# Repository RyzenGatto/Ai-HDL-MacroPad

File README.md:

# AI-HDL-MacroPad
Application Specific nRF52840 OR RP2040 based Keyboards for the PRISM Lab at the University of Arizona

Below are 3D renders. Schematic for the latest version is available in the Repo.

NOTE: If you want to adapt this to your own project with more keys, get familiar with KiCad and learn keyboard matrices (KMK has a good guide in their repo). 

## Info

KiCad files can be found in its folder. Production files can be found in Export Files. Version 1 is a super simple 5-key design for use with a XIAO RP2040. It does not have Bluetooth. It's also much cheaper. 
Version 1.5 has BT and a lithium-ion battery and relies on the KMK firmware.

## Version 2.4 
Fully integrated Macro Design. This design has been optimized for long-term reliability and has been simplified. A test PCB is accessible in the V2 kicad folders

## Old Versions
**Version 1**
This is the cheapest version. It can be assembled by hand, no BOM or pick and place needed.

**Version 1.5**
Basically V1 but with BLE and a battery and M2 2.2mm screws.

**Version 2.3 (Test PCB)**

# TO DO

1. Write software using KMK firmware

~~2. Determine Key Caps~~ DONE

~~3. Develop wifi version with battery + BT~~ DONE

4.  PROTOTYPE!

# Materials
ONLY FOR V1.5
| Item  | Quantity | Link |
| ------------- | ------------- | ---- |
| seeed studio XIAO nRF52840  | 1  | [Mouser](https://www.mouser.com/ProductDetail/Seeed-Studio/102010448?qs=Znm5pLBrcAJ5g%252BWAkitg4w%3D%3D)     |
| Cherry MX Switches  | 6  |  [Mouser](https://www.mouser.com/ProductDetail/CHERRY/MX1A-C1NW?qs=sGAEpiMZZMtFyPk3yBMYYJ6eFtqPPgccKDEfiw%252Brqds%3D)    |
| Lithium-Ion Battery | 1 | [Option 1](https://www.digikey.com/en/products/detail/sparkfun-electronics/PRT-13851/6605199) [Option 2](https://www.digikey.com/en/products/detail/adafruit-industries-llc/258/5054544) |
| Battery connector | 1 | [Mouser](https://www.digikey.com/en/products/detail/jst-sales-america-inc/S2B-PH-K-S/926626) |
| Battery LED | 1 | [Mouser](https://www.digikey.com/en/products/detail/sparkfun-electronics/COM-16347/11630204)

2.xx Materials are available in the BOM of the KiCad Files.

# Firmware

This project will use the [KMK Firmware](https://github.com/KMKfw/kmk_firmware).
KMK has its own license, please refer to their page for more details. KMK has a GUI interface that another developer made.

This [battery management](https://github.com/Tjoms99/xiao_sense_nrf52840_battery_lib) software will be used to communicate battery life and charge status to the user.

Software by [this guy](https://github.com/ernesto-martinez1)

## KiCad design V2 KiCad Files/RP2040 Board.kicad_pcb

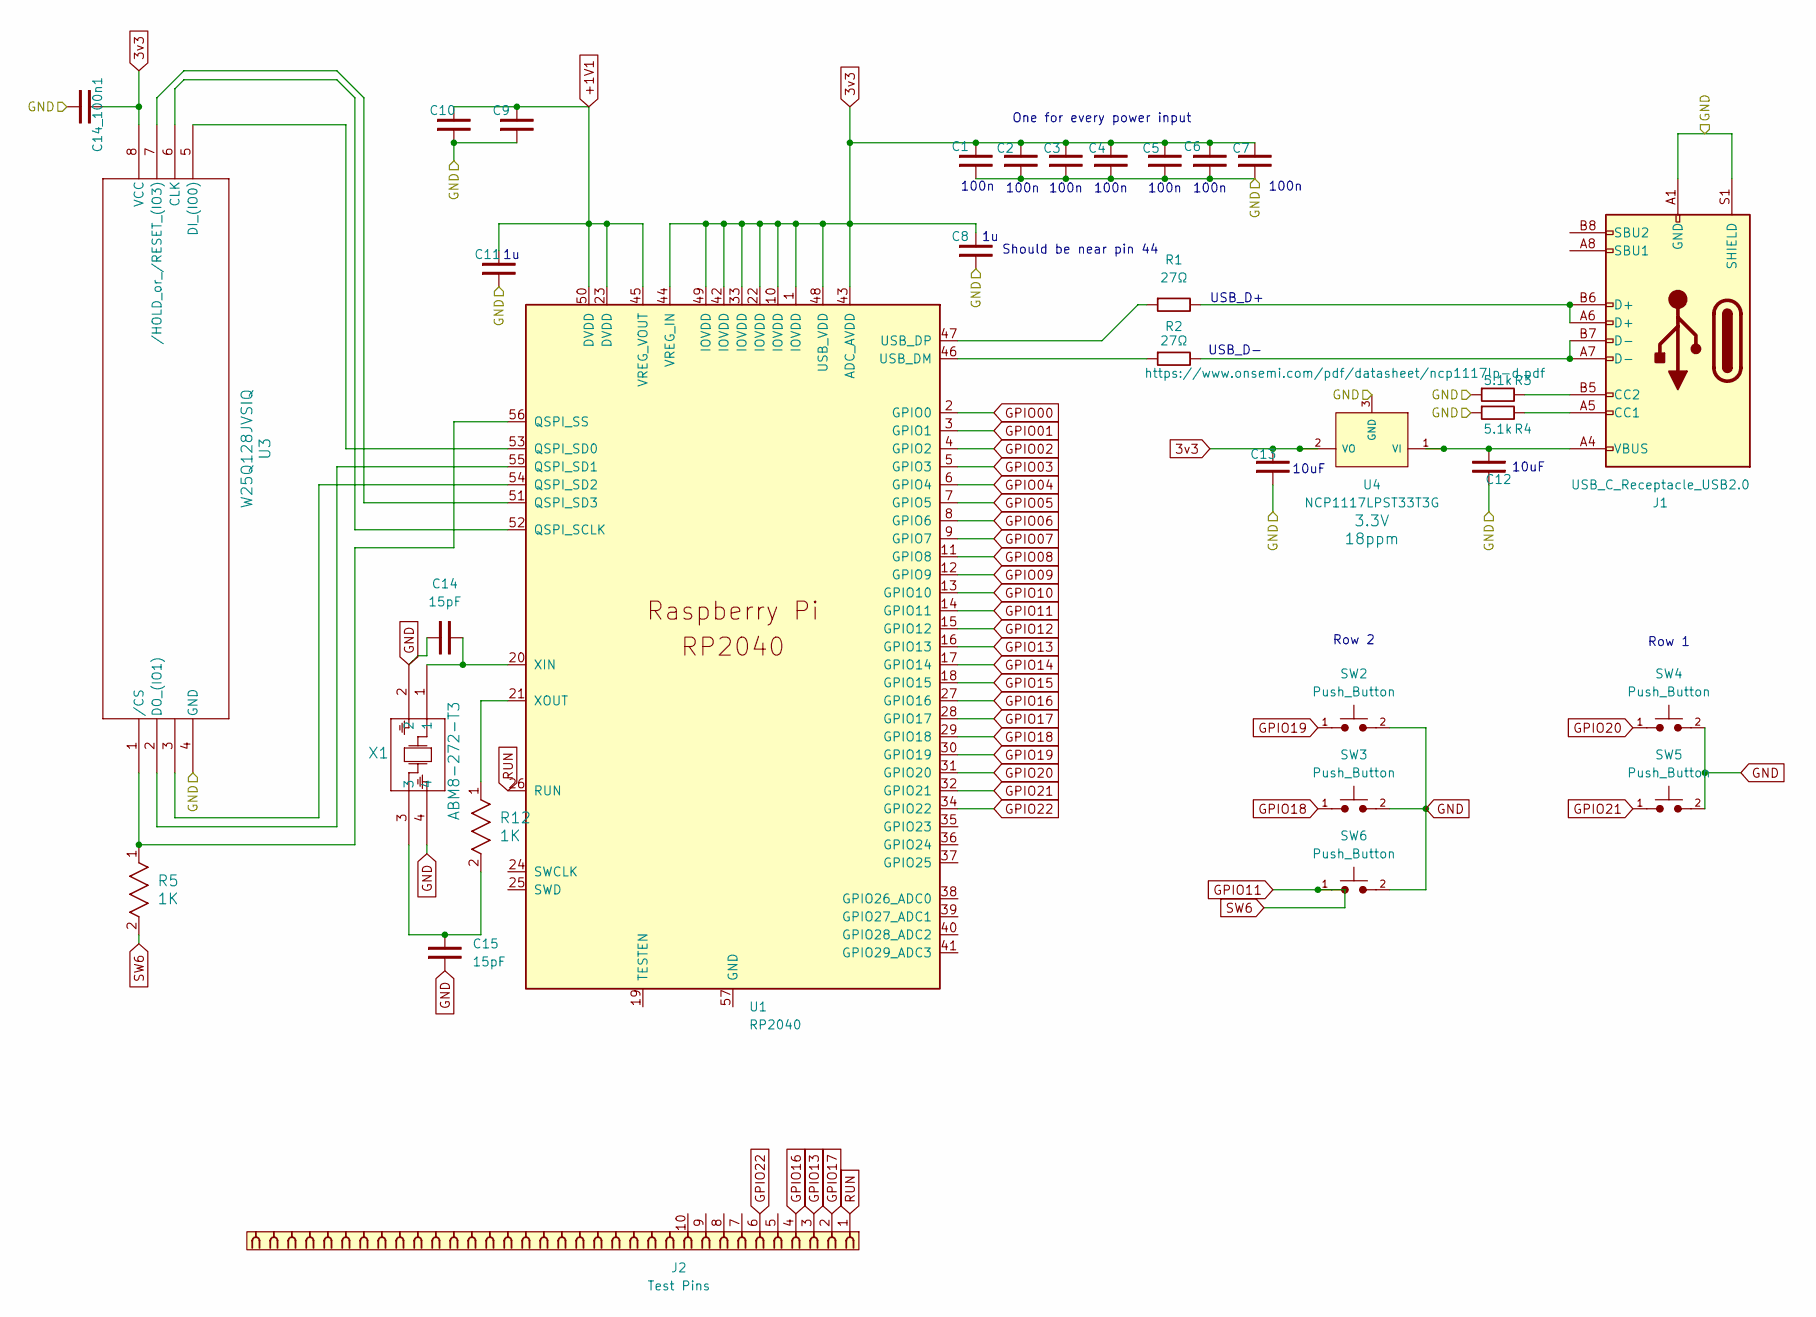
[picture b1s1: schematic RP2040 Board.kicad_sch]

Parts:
C1, C2, C3, C4, C5, C6, C7, C9, C10, C14_100n1: 100nF; C_0603_1608Metric; Part Number CL10E104KC8VPNC
C8, C11: 1uF; C_0603_1608Metric; Part Number CL10B105KP8NNNC
C12, C13: 10uF; C_0603_1608Metric; Part Number CL10A106MQ8NNNC
C14, C15: 15pF; C_0603_1608Metric; Part Number 885012006003
J1: USB_C_Receptacle_USB2.0; USB_C_Receptacle_G-Switch_GT-USB-7010ASV; Part Number GT-USB-7010ASV; LCSC C165948
J2: Test Pins
R1, R2: 27Ω; R_0402_1005Metric; Part Number ERJ-2RKF27R0X
R3, R4: 5.1k; R_0402_1005Metric; Part Number ERA-2AEB512X
R5, R12: 1K; RC0402N_PAN; Part Number ERJ-2RKF1001X
SW2, SW3, SW4, SW5, SW6: Push_Button; SW_Cherry_MX_1.00u_PCB; Part Number MX1A-C1NW
U1: RP2040; RP2040-QFN-56; Part Number SC0914(13)
U3: W25Q128JVSIQ; SOIC-8-1EP_3.9x4.9mm_P1.27mm_EP2.29x3mm; Part Number W25Q128JVSIQ
U4: NCP1117LPST33T3G; NCP1117; Part Number NCP1117LPST33T3G; JLCPCB ID C233715
X1: ABM8-272-T3; ABM8-272-T3_ABR; Part Number ABM8-272-T3

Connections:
3v3: C1.2, C2.2, C3.2, C4.2, C5.2, C6.2, C7.2, C8.2, C13.2, C14_100n1.2, U1.1 (IOVDD), U1.10 (IOVDD), U1.22 (IOVDD), U1.33 (IOVDD), U1.42 (IOVDD), U1.43 (ADC_AVDD), U1.44 (VREG_IN), U1.48 (USB_VDD), U1.49 (IOVDD), U3.8 (VCC), U4.2 (VO)
+1V1: C9.2, C10.2, C11.2, U1.23 (DVDD), U1.45 (VREG_VOUT), U1.50 (DVDD)
GND: C1.1, C2.1, C3.1, C4.1, C5.1, C6.1, C7.1, C8.1, C9.1, C10.1, C11.1, C12.2, C13.1, C14.1, C14_100n1.1, C15.1, J1.A1 (GND), J1.A12 (GND), J1.B1 (GND), J1.B12 (GND), J1.S1 (SHIELD), R3.1, R4.1, SW2.2, SW3.2, SW4.2, SW5.2, SW6.2, U1.57 (GND), U1.GND, U3.4 (GND), U4.3 (GND), X1.2, X1.4
GPIO00: U1.2 (GPIO0)
GPIO01: U1.3 (GPIO1)
GPIO02: U1.4 (GPIO2)
GPIO03: U1.5 (GPIO3)
GPIO04: U1.6 (GPIO4)
GPIO05: U1.7 (GPIO5)
GPIO06: U1.8 (GPIO6)
GPIO07: U1.9 (GPIO7)
GPIO08: U1.11 (GPIO8)
GPIO09: U1.12 (GPIO9)
GPIO10: U1.13 (GPIO10)
GPIO11: R5.2, SW6.1, U1.14 (GPIO11)
GPIO12: U1.15 (GPIO12)
GPIO13: J2.3, U1.16 (GPIO13)
GPIO14: U1.17 (GPIO14)
GPIO15: U1.18 (GPIO15)
GPIO16: J2.4, U1.27 (GPIO16)
GPIO17: J2.2, U1.28 (GPIO17)
GPIO18: SW3.1, U1.29 (GPIO18)
GPIO19: SW2.1, U1.30 (GPIO19)
GPIO20: SW4.1, U1.31 (GPIO20)
GPIO21: SW5.1, U1.32 (GPIO21)
GPIO22: J2.6, U1.34 (GPIO22)
unnamed: C15.2, R12.2, X1.3
unnamed: J1.A5 (CC1), R4.2
unnamed: J1.B5 (CC2), R3.2
unnamed: J1.A6 (D+), J1.B6 (D+), R1.2
unnamed: J1.A7 (D-), J1.B7 (D-), R2.2
unnamed: U1.52 (QSPI_SCLK), U3.6 (CLK)
unnamed: U1.53 (QSPI_SD0), U3.5 (DI_(IO0))
unnamed: U1.55 (QSPI_SD1), U3.2 (DO_(IO1))
unnamed: U1.54 (QSPI_SD2), U3.3
unnamed: U1.51 (QSPI_SD3), U3.7 (/HOLD_or_/RESET_(IO3))
unnamed: R5.1, U1.56 (QSPI_SS), U3.1 (/CS)
unnamed: R2.1, U1.46 (USB_DM)
unnamed: R1.1, U1.47 (USB_DP)
unnamed: C14.2, U1.20 (XIN), X1.1
unnamed: R12.1, U1.21 (XOUT)
unnamed: C12.1, J1.A4 (VBUS), J1.A9 (VBUS), J1.B4 (VBUS), J1.B9 (VBUS), U4.1 (VI)
RUN: J2.1, U1.26 (RUN)

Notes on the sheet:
100n
One for every power input
Should be near pin 44
10uF
Row 1
Row 2
USB_D-
USB_D+

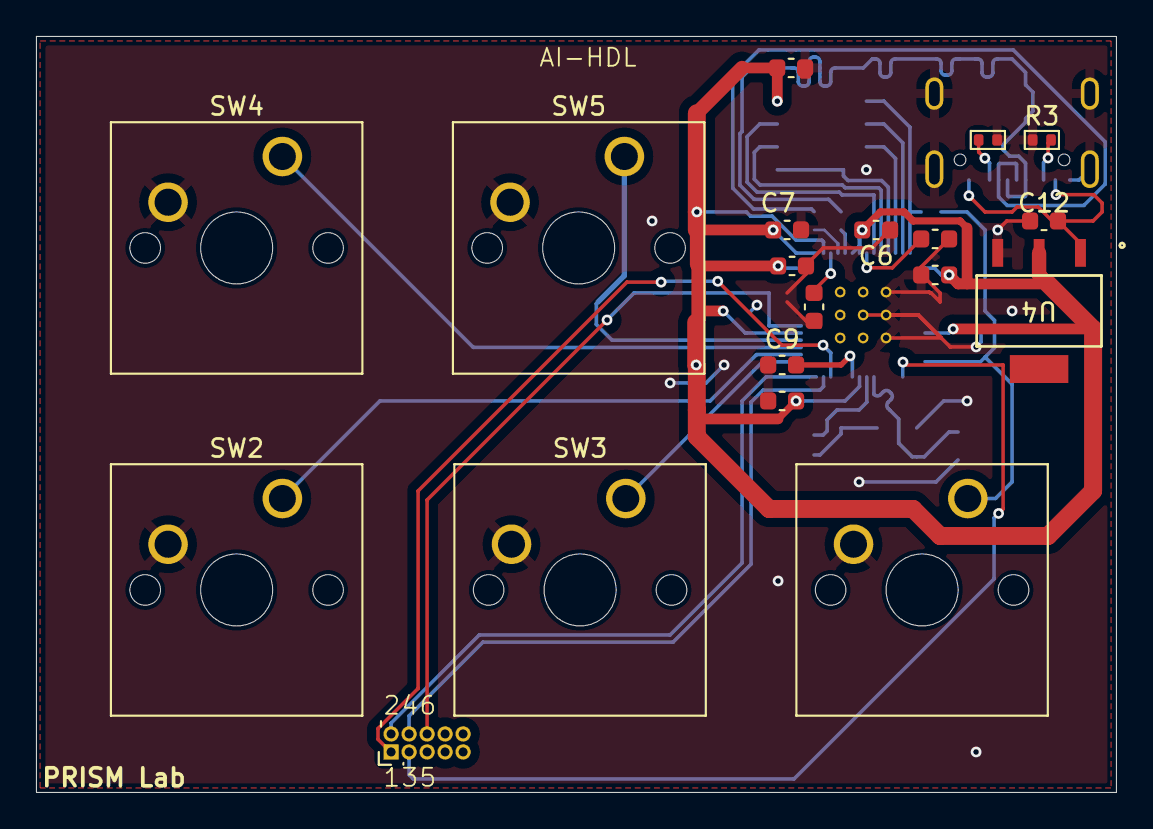
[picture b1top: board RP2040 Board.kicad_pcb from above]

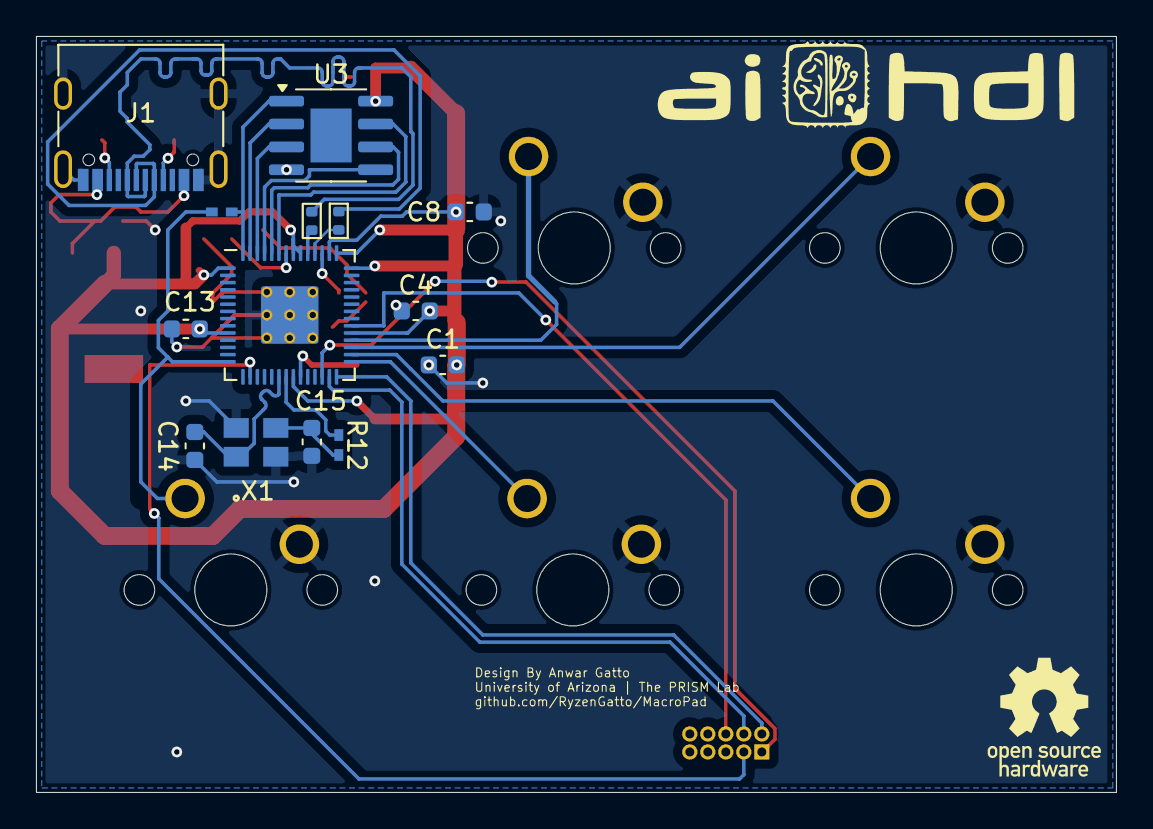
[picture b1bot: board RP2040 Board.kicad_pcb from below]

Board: 2 copper layers, 60.0 x 42.0 mm, 33 parts (14 on the bottom side), 29 nets.

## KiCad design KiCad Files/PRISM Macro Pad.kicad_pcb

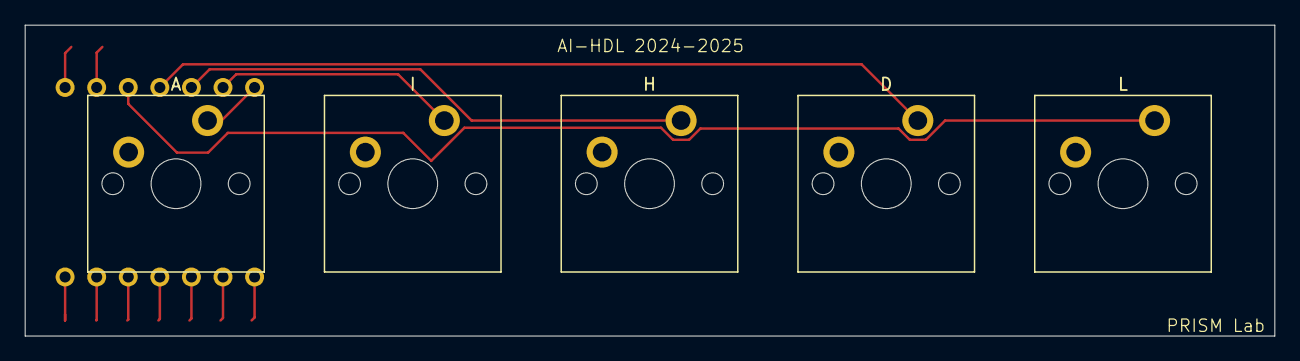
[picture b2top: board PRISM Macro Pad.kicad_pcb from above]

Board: 2 copper layers, 100.5 x 25.0 mm, 6 parts (1 on the bottom side), 6 nets.

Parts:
A: Push_Button; SW_Cherry_MX_PCB_1.00u
D: Push_Button; SW_Cherry_MX_PCB_1.00u
H: Push_Button; SW_Cherry_MX_PCB_1.00u
I: Push_Button; SW_Cherry_MX_PCB_1.00u
L: Push_Button; SW_Cherry_MX_PCB_1.00u
U1: Seeed Studio XIAO RP2040; XIAO-RP2040-DIP

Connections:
unnamed: A.1, D.1, H.1, I.1, L.1, U1.12 (3V3)
unnamed: H.2, U1.5 (PA8_A4_D4_SDA)
unnamed: I.2, U1.6 (PA9_A5_D5_SCL)
unnamed: L.2, U1.3 (PA10_A2_D2)
unnamed: D.2, U1.4 (PA11_A3_D3)
unnamed: A.2, U1.7 (PB08_A6_D6_TX)

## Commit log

2024-11-17 Update LICENSE
2024-11-24 Create V2
2024-11-25 Update README.md
    Added V2.1 info
2024-12-21 New Test Board
    Cleaned up traces, added BOM into KiCad, reduced production costs
